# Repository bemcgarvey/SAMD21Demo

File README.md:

# SAMD21Demo
 
## A demonstartion board for the ATSAMD21G18A microcontroller.  Includes firmware projects to demonstrate many modules and features.  
  
### There is sample firmware for:
* Basic gpio and interrupts
* Sleepwalking
* Analog comparator
* PWM h-bridge control
* USB MSD device
* I2C LCD

### All firmware is built in MPLabX with MPLab Harmony 3 and the XC32 compiler.  
### Schematic and PCB were made with KiCAD

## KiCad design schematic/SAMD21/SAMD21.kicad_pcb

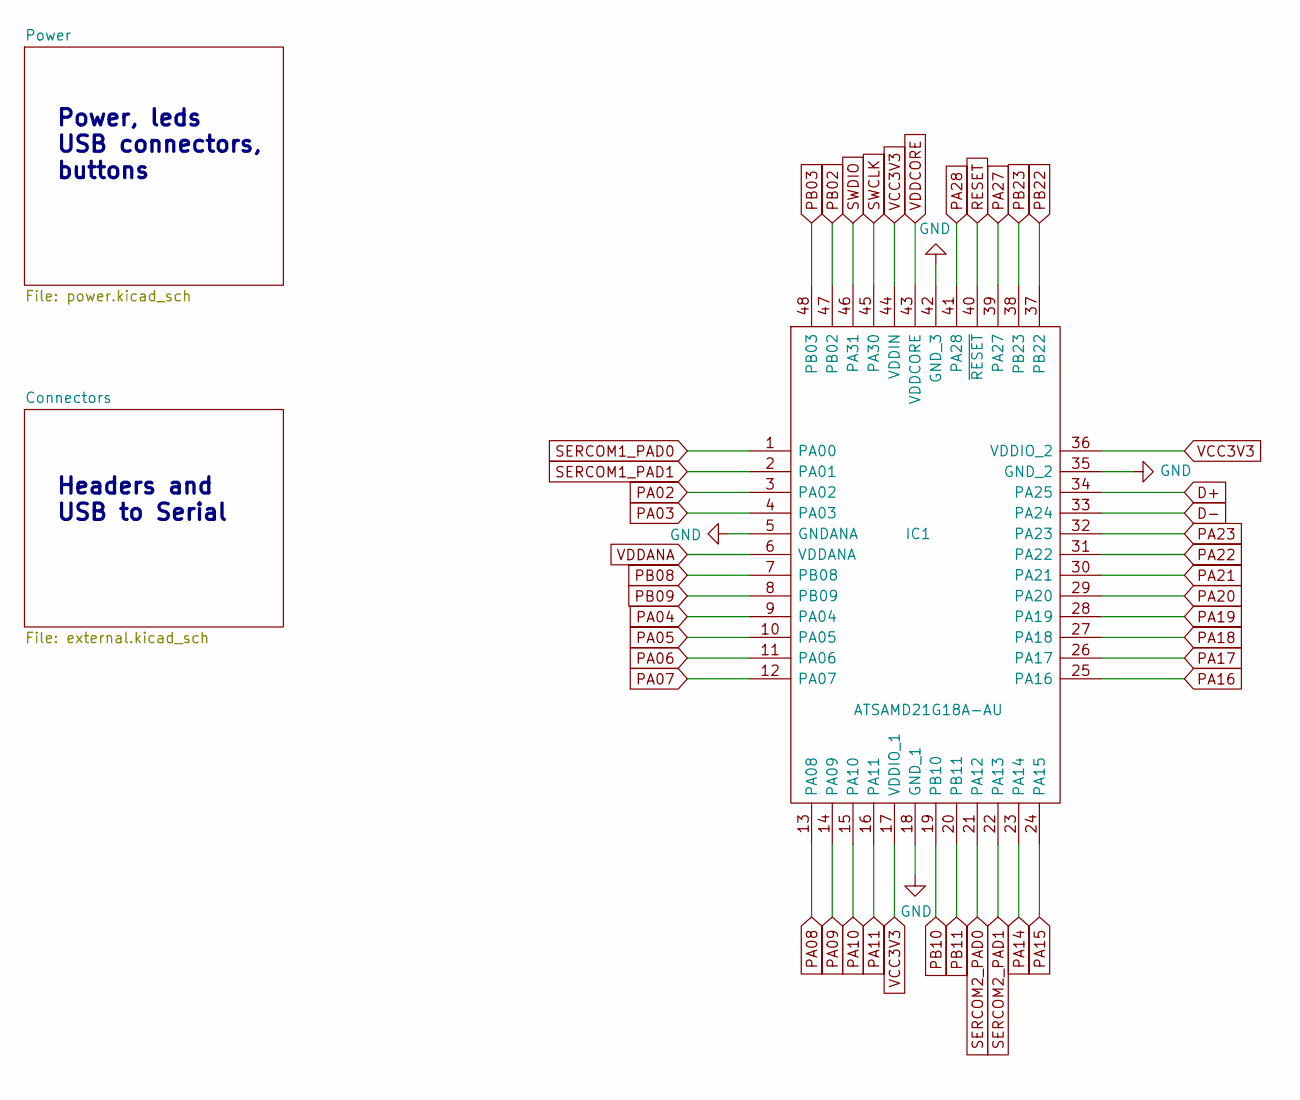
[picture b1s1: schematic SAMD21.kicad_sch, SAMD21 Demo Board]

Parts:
IC1: ATSAMD21G18A-AU; QFP50P900X900X120-48N; Mouser Part Number 556-ATSAMD21G18A-AU

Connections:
D+: IC1.34 (PA25); also elsewhere on the board
D-: IC1.33 (PA24); also elsewhere on the board
GND: IC1.5 (GNDANA), IC1.18 (GND_1), IC1.35 (GND_2), IC1.42 (GND_3); also elsewhere on the board
PA02: IC1.3 (PA02); also elsewhere on the board
PA03: IC1.4 (PA03); also elsewhere on the board
PA04: IC1.9 (PA04); also elsewhere on the board
PA05: IC1.10 (PA05); also elsewhere on the board
PA06: IC1.11 (PA06); also elsewhere on the board
PA07: IC1.12 (PA07); also elsewhere on the board
PA08: IC1.13 (PA08); also elsewhere on the board
PA09: IC1.14 (PA09); also elsewhere on the board
PA10: IC1.15 (PA10); also elsewhere on the board
PA11: IC1.16 (PA11); also elsewhere on the board
PA14: IC1.23 (PA14); also elsewhere on the board
PA15: IC1.24 (PA15); also elsewhere on the board
PA16: IC1.25 (PA16); also elsewhere on the board
PA17: IC1.26 (PA17); also elsewhere on the board
PA18: IC1.27 (PA18); also elsewhere on the board
PA19: IC1.28 (PA19); also elsewhere on the board
PA20: IC1.29 (PA20); also elsewhere on the board
PA21: IC1.30 (PA21); also elsewhere on the board
PA22: IC1.31 (PA22); also elsewhere on the board
PA23: IC1.32 (PA23); also elsewhere on the board
PA27: IC1.39 (PA27); also elsewhere on the board
PA28: IC1.41 (PA28); also elsewhere on the board
PB02: IC1.47 (PB02); also elsewhere on the board
PB03: IC1.48 (PB03); also elsewhere on the board
PB08: IC1.7 (PB08); also elsewhere on the board
PB09: IC1.8 (PB09); also elsewhere on the board
PB10: IC1.19 (PB10); also elsewhere on the board
PB11: IC1.20 (PB11); also elsewhere on the board
PB22: IC1.37 (PB22); also elsewhere on the board
PB23: IC1.38 (PB23); also elsewhere on the board
RESET: IC1.40 (~RESET); also elsewhere on the board
SERCOM1_PAD0: IC1.1 (PA00); also elsewhere on the board
SERCOM1_PAD1: IC1.2 (PA01); also elsewhere on the board
SERCOM2_PAD0: IC1.21 (PA12); also elsewhere on the board
SERCOM2_PAD1: IC1.22 (PA13); also elsewhere on the board
SWCLK: IC1.45 (PA30); also elsewhere on the board
SWDIO: IC1.46 (PA31); also elsewhere on the board
VCC3V3: IC1.17 (VDDIO_1), IC1.36 (VDDIO_2), IC1.44 (VDDIN); also elsewhere on the board
VDDANA: IC1.6 (VDDANA); also elsewhere on the board
VDDCORE: IC1.43 (VDDCORE); also elsewhere on the board

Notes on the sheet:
Headers and USB to Serial
Power, leds USB connectors, buttons

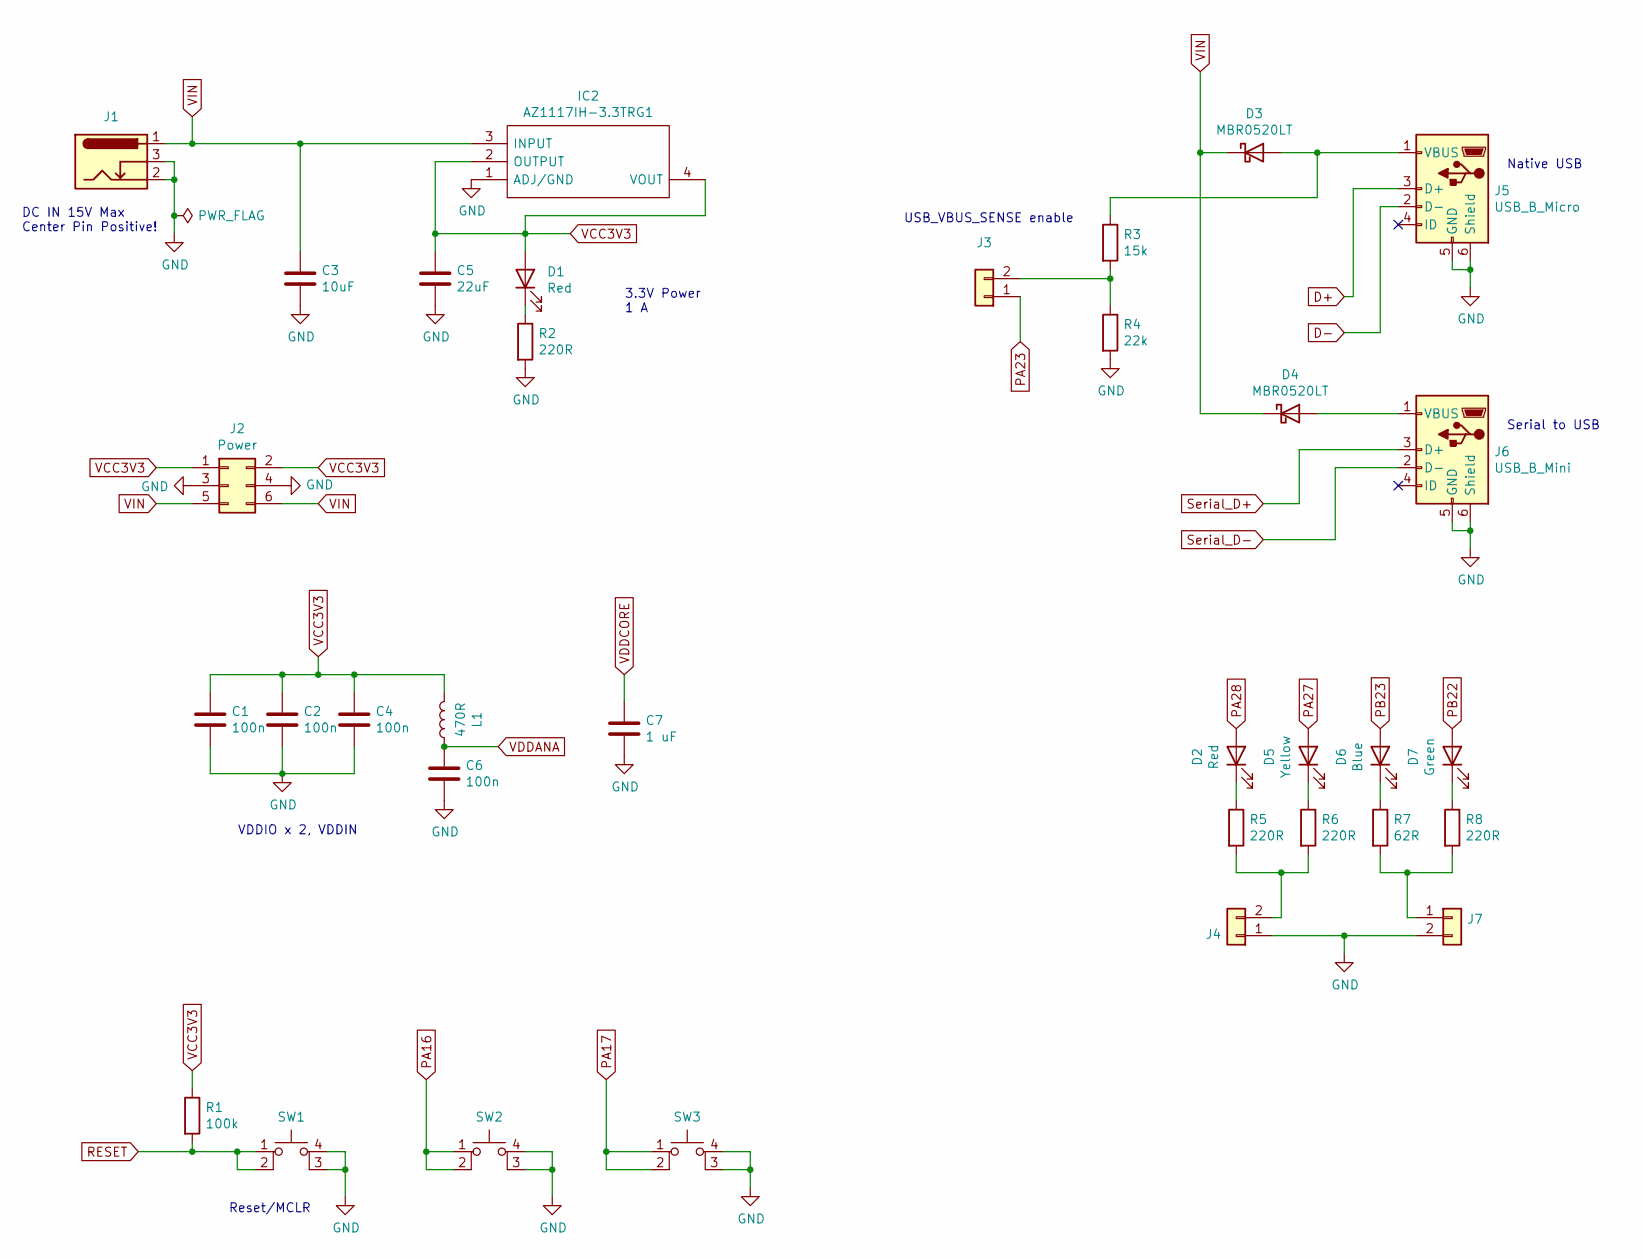
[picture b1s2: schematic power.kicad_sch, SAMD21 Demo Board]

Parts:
C1, C2, C4, C6: 100n; C_0402_1005Metric
C3: 10uF; C_0805_2012Metric
C5: 22uF; C_0603_1608Metric
C7: 1 uF; C_0402_1005Metric
D1: Red; LED_0603_1608Metric
D2: Red; LED_0805_2012Metric
D3, D4: MBR0520LT; D_SOD-123
D5: Yellow; LED_0805_2012Metric
D6: Blue; LED_0805_2012Metric
D7: Green; LED_0805_2012Metric
IC2: AZ1117IH-3.3TRG1; SOT230P700X180-4N; Mouser Part Number 621-AZ1117IH-3.3TRG1
J1: Barrel_Jack_Switch; BarrelJack_Wuerth_6941xx301002
J2: Power; PinHeader_2x03_P2.54mm_Vertical
J3, J4, J7: Conn_01x02; PinHeader_1x02_P2.54mm_Vertical
J5: USB_B_Micro; USB_Micro-B_Amphenol_10118194_Horizontal
J6: USB_B_Mini; USB_Mini-B_Wuerth_65100516121_Horizontal
L1: 470R; L_0603_1608Metric
R1: 100k; R_0603_1608Metric
R2, R5, R6, R8: 220R; R_0603_1608Metric
R3: 15k; R_0603_1608Metric
R4: 22k; R_0603_1608Metric
R7: 62R; R_0603_1608Metric
SW1: SW_MEC_5E; PTS647SK38SMTR2LFS
SW2, SW3: SW_MEC_5E; FSM16JH

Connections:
D+: J5.3 (D+); also elsewhere on the board
D-: J5.2 (D-); also elsewhere on the board
GND: C1.2, C2.2, C3.2, C4.2, C5.2, C6.2, C7.2, IC2.1 (ADJ/GND), J1.2, J1.3, J2.3, J2.4, J4.1, J5.5 (GND), J5.6 (Shield), J6.5 (GND), J6.6 (Shield), J7.2, R2.2, R4.2, SW1.3 (K), SW1.4 (A), SW2.3 (K), SW2.4 (A), SW3.3 (K), SW3.4 (A); also elsewhere on the board
unnamed: D1.1 (K), R2.1
unnamed: D2.1 (K), R5.1
unnamed: D3.2 (A), J5.1 (VBUS), R3.1
unnamed: D4.2 (A), J6.1 (VBUS)
unnamed: D5.1 (K), R6.1
unnamed: D6.1 (K), R7.1
unnamed: D7.1 (K), R8.1
unnamed: J3.2, R3.2, R4.1
unnamed: J4.2, R5.2, R6.2
unnamed: J7.1, R7.2, R8.2
PA16: SW2.1, SW2.2; also elsewhere on the board
PA17: SW3.1, SW3.2; also elsewhere on the board
PA23: J3.1; also elsewhere on the board
PA27: D5.2 (A); also elsewhere on the board
PA28: D2.2 (A); also elsewhere on the board
PB22: D7.2 (A); also elsewhere on the board
PB23: D6.2 (A); also elsewhere on the board
RESET: R1.2, SW1.1, SW1.2; also elsewhere on the board
Serial_D+: J6.3 (D+); also elsewhere on the board
Serial_D-: J6.2 (D-); also elsewhere on the board
VCC3V3: C1.1, C2.1, C4.1, C5.1, D1.2 (A), IC2.2 (OUTPUT), IC2.4 (VOUT), J2.1, J2.2, L1.2, R1.1; also elsewhere on the board
VDDANA: C6.1, L1.1; also elsewhere on the board
VDDCORE: C7.1; also elsewhere on the board
VIN: C3.1, D3.1 (K), D4.1 (K), IC2.3 (INPUT), J1.1, J2.5, J2.6

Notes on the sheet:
3.3V Power 1 A
Reset/MCLR
VDDIO x 2, VDDIN
Serial to USB
USB_VBUS_SENSE enable
DC IN 15V Max Center Pin Positive!
Native USB

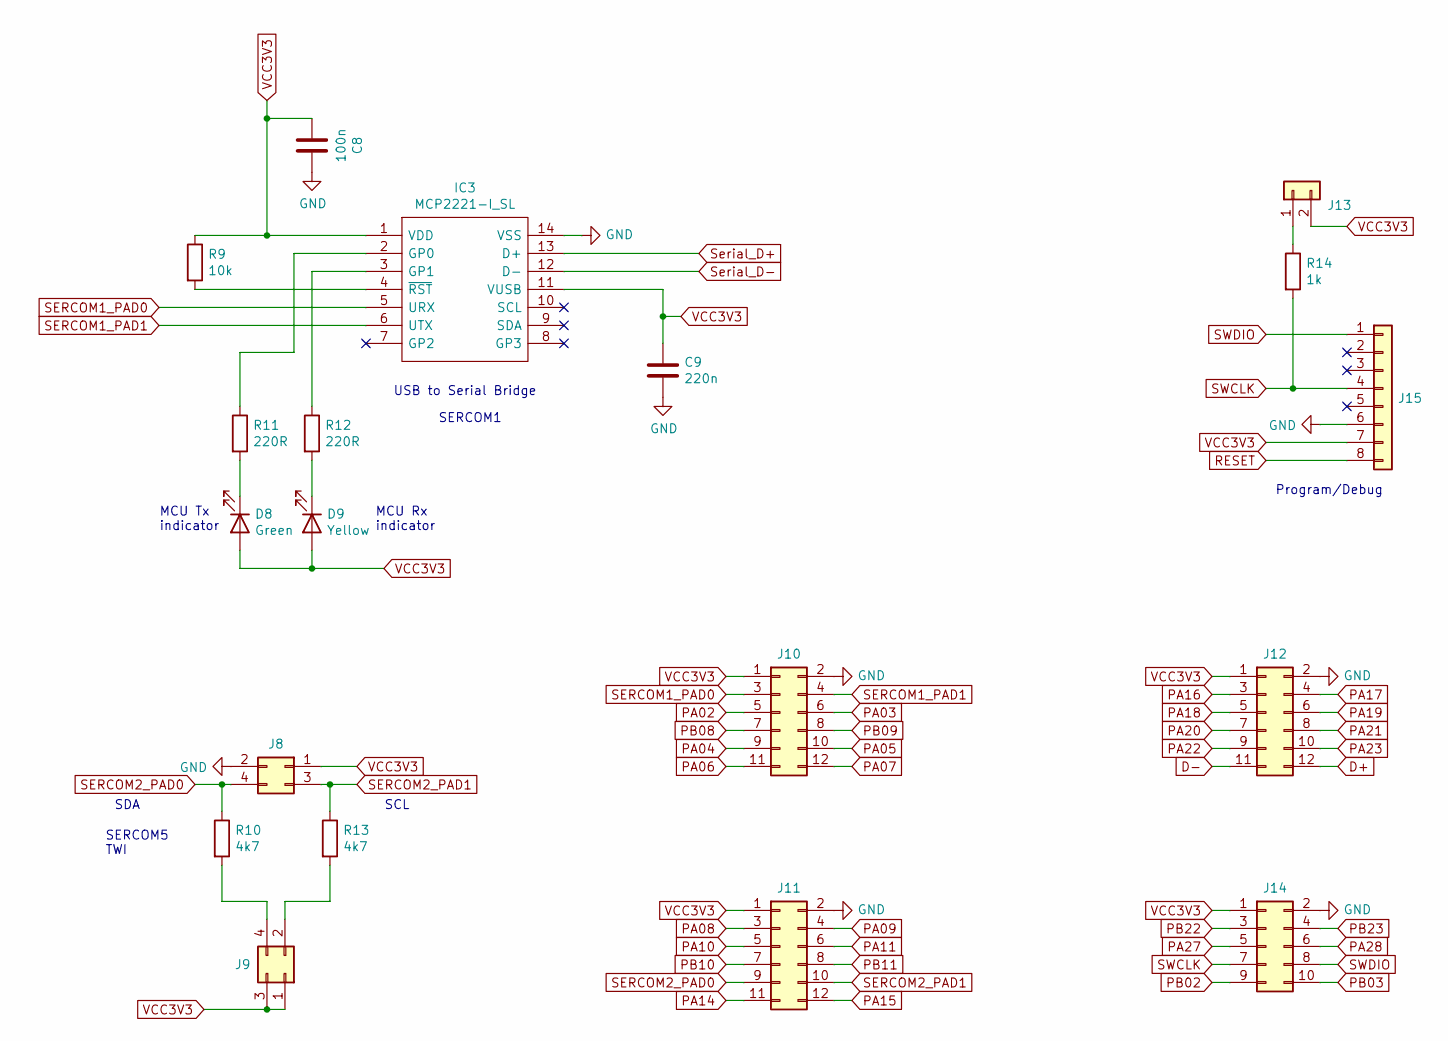
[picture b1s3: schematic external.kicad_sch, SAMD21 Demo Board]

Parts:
C8: 100n; C_0603_1608Metric
C9: 220n; C_0603_1608Metric
D8: Green; LED_0603_1608Metric
D9: Yellow; LED_0603_1608Metric
IC3: MCP2221-I_SL; SOIC127P600X175-14N; Mouser Part Number 579-MCP2221-I/SL
J8, J9: Conn_02x02_Odd_Even; PinHeader_2x02_P2.54mm_Vertical
J10, J11, J12: Conn_02x06_Odd_Even; PinHeader_2x06_P2.54mm_Vertical
J13: Conn_01x02; PinHeader_1x02_P2.54mm_Vertical
J14: Conn_02x05_Odd_Even; PinHeader_2x05_P2.54mm_Vertical
J15: Conn_01x08; PinHeader_1x08_P2.54mm_Horizontal
R9: 10k; R_0603_1608Metric
R10, R13: 4k7; R_0603_1608Metric
R11, R12: 220R; R_0603_1608Metric
R14: 1k; R_0603_1608Metric

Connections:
D+: J12.12; also elsewhere on the board
D-: J12.11; also elsewhere on the board
GND: C8.1, C9.2, IC3.14 (VSS), J8.2, J10.2, J11.2, J12.2, J14.2, J15.6; also elsewhere on the board
unnamed: D8.1 (K), R11.2
unnamed: D9.1 (K), R12.2
unnamed: IC3.2 (GP0), R11.1
unnamed: IC3.3 (GP1), R12.1
unnamed: IC3.4 (~RST), R9.2
unnamed: J9.2, R13.2
unnamed: J9.4, R10.2
unnamed: J13.1, R14.1
PA02: J10.5; also elsewhere on the board
PA03: J10.6; also elsewhere on the board
PA04: J10.9; also elsewhere on the board
PA05: J10.10; also elsewhere on the board
PA06: J10.11; also elsewhere on the board
PA07: J10.12; also elsewhere on the board
PA08: J11.3; also elsewhere on the board
PA09: J11.4; also elsewhere on the board
PA10: J11.5; also elsewhere on the board
PA11: J11.6; also elsewhere on the board
PA14: J11.11; also elsewhere on the board
PA15: J11.12; also elsewhere on the board
PA16: J12.3; also elsewhere on the board
PA17: J12.4; also elsewhere on the board
PA18: J12.5; also elsewhere on the board
PA19: J12.6; also elsewhere on the board
PA20: J12.7; also elsewhere on the board
PA21: J12.8; also elsewhere on the board
PA22: J12.9; also elsewhere on the board
PA23: J12.10; also elsewhere on the board
PA27: J14.5; also elsewhere on the board
PA28: J14.6; also elsewhere on the board
PB02: J14.9; also elsewhere on the board
PB03: J14.10; also elsewhere on the board
PB08: J10.7; also elsewhere on the board
PB09: J10.8; also elsewhere on the board
PB10: J11.7; also elsewhere on the board
PB11: J11.8; also elsewhere on the board
PB22: J14.3; also elsewhere on the board
PB23: J14.4; also elsewhere on the board
RESET: J15.8; also elsewhere on the board
SERCOM1_PAD0: IC3.5 (URX), J10.3; also elsewhere on the board
SERCOM1_PAD1: IC3.6 (UTX), J10.4; also elsewhere on the board
SERCOM2_PAD0: J8.4, J11.9, R10.1; also elsewhere on the board
SERCOM2_PAD1: J8.3, J11.10, R13.1; also elsewhere on the board
SWCLK: J14.7, J15.4, R14.2; also elsewhere on the board
SWDIO: J14.8, J15.1; also elsewhere on the board
Serial_D+: IC3.13 (D+); also elsewhere on the board
Serial_D-: IC3.12 (D-); also elsewhere on the board
VCC3V3: C8.2, C9.1, D8.2 (A), D9.2 (A), IC3.1 (VDD), IC3.11 (VUSB), J8.1, J9.1, J9.3, J10.1, J11.1, J12.1, J13.2, J14.1, J15.7, R9.1; also elsewhere on the board

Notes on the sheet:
MCU Tx indicator
SCL
USB to Serial Bridge
SDA
MCU Rx indicator
SERCOM5 TWI
Program/Debug
SERCOM1

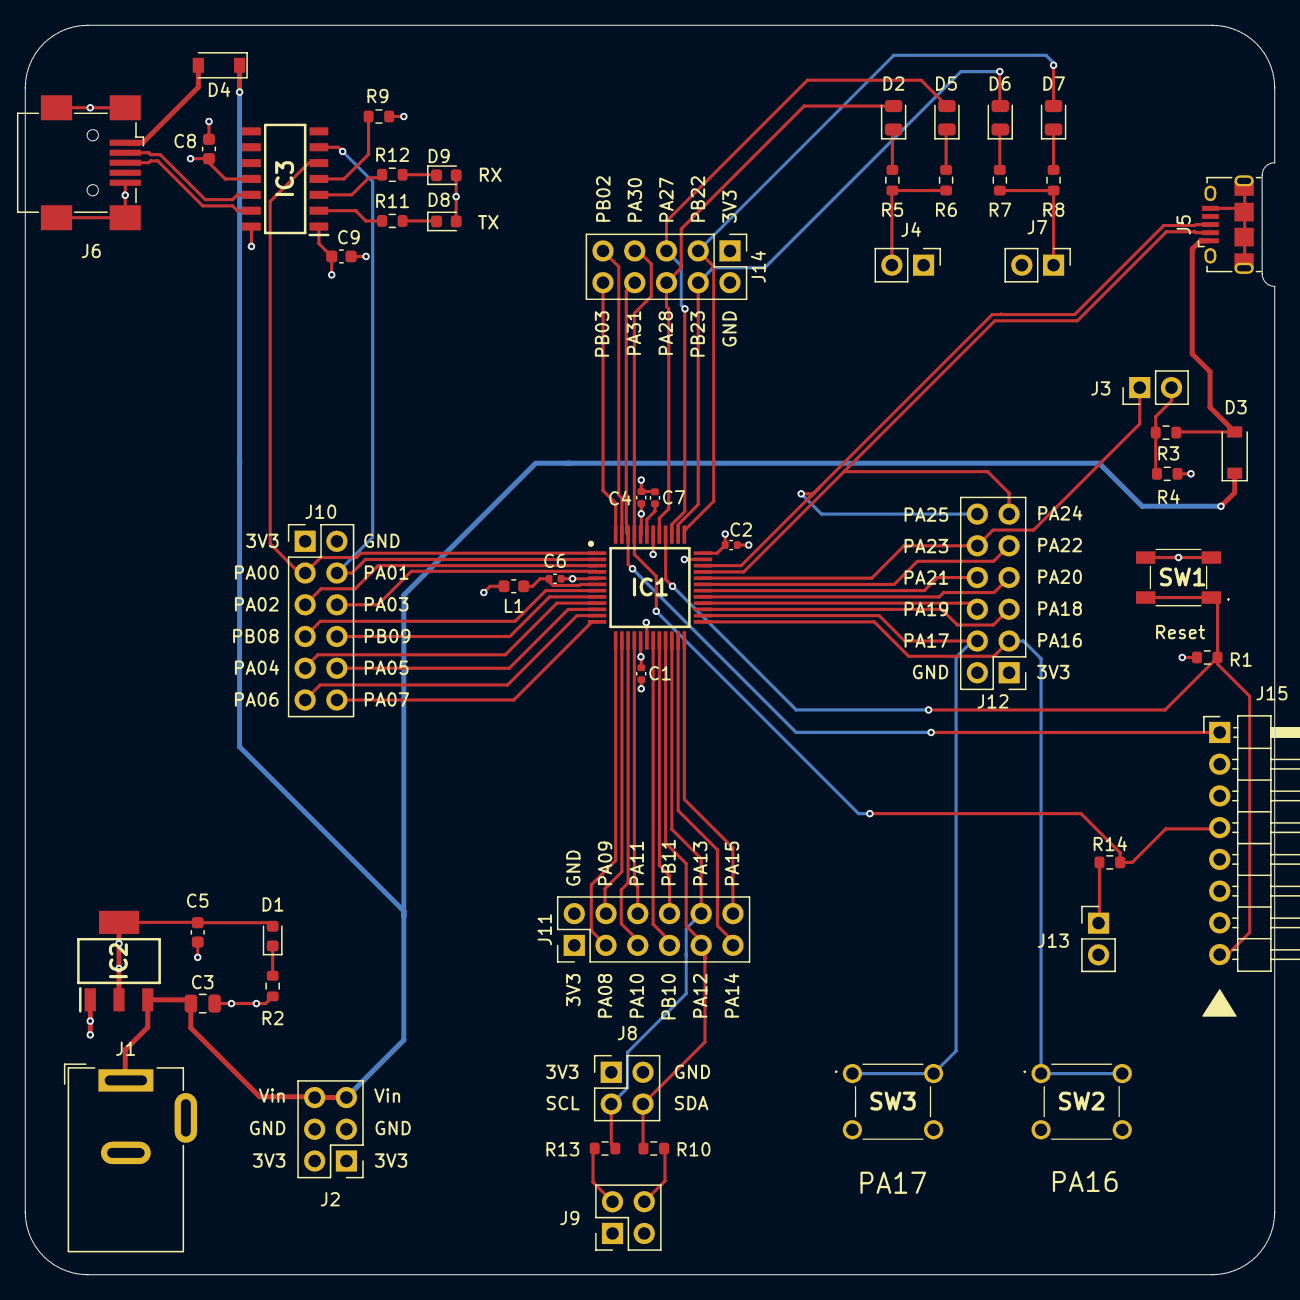
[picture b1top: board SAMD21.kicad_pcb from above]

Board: 4 copper layers, 100.0 x 100.0 mm, 54 parts (0 on the bottom side), 64 nets.

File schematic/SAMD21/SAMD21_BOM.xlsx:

Ref | Qnty | Value | Footprint
C1, C2, C4, C6, | 4 | 100n | Capacitor_SMD:C_0402_1005Metric
C3, | 1 | 10uF | Capacitor_SMD:C_0805_2012Metric
C5, | 1 | 22uF | Capacitor_SMD:C_0603_1608Metric
C7, | 1 | 1 uF | Capacitor_SMD:C_0402_1005Metric
C8, | 1 | 100n | Capacitor_SMD:C_0603_1608Metric
C9, | 1 | 220n | Capacitor_SMD:C_0603_1608Metric
D1, | 1 | Red | LED_SMD:LED_0603_1608Metric
D2, | 1 | Red | LED_SMD:LED_0805_2012Metric
D3, D4, | 2 | MBR0520LT | Diode_SMD:D_SOD-123
D5, | 1 | Yellow | LED_SMD:LED_0805_2012Metric
D6, | 1 | Blue | LED_SMD:LED_0805_2012Metric
D7, | 1 | Green | LED_SMD:LED_0805_2012Metric
D8, | 1 | Green | LED_SMD:LED_0603_1608Metric
D9, | 1 | Yellow | LED_SMD:LED_0603_1608Metric
IC1, | 1 | ATSAMD21G18A-AU | SamacSys_Parts:QFP50P900X900X120-48N
IC2, | 1 | AZ1117IH-3.3TRG1 | SamacSys_Parts:SOT230P700X180-4N
IC3, | 1 | MCP2221-I_SL | SamacSys_Parts:SOIC127P600X175-14N
J1, | 1 | Barrel_Jack_Switch | Connector_BarrelJack:BarrelJack_Wuerth_6941xx301002
J2, | 1 | Power | Connector_PinHeader_2.54mm:PinHeader_2x03_P2.54mm_Vertical
J3, J4, J7, J13, | 4 | Conn_01x02 | Connector_PinHeader_2.54mm:PinHeader_1x02_P2.54mm_Vertical
J5, | 1 | USB_B_Micro | Connector_USB:USB_Micro-B_Amphenol_10118194_Horizontal
J6, | 1 | USB_B_Mini | Connector_USB:USB_Mini-B_Wuerth_65100516121_Horizontal
J8, J9, | 2 | Conn_02x02_Odd_Even | Connector_PinHeader_2.54mm:PinHeader_2x02_P2.54mm_Vertical
J10, J11, J12, | 3 | Conn_02x06_Odd_Even | Connector_PinHeader_2.54mm:PinHeader_2x06_P2.54mm_Vertical
J14, | 1 | Conn_02x05_Odd_Even | Connector_PinHeader_2.54mm:PinHeader_2x05_P2.54mm_Vertical
J15, | 1 | Conn_01x08 | Connector_PinHeader_2.54mm:PinHeader_1x08_P2.54mm_Horizontal
L1, | 1 | 470R | Inductor_SMD:L_0603_1608Metric
R1, | 1 | 100k | Resistor_SMD:R_0603_1608Metric
R2, R5, R6, R8, R11, R12, | 6 | 220R | Resistor_SMD:R_0603_1608Metric
R3, | 1 | 15k | Resistor_SMD:R_0603_1608Metric
R4, | 1 | 22k | Resistor_SMD:R_0603_1608Metric
R7, | 1 | 62R | Resistor_SMD:R_0603_1608Metric
R9, | 1 | 10k | Resistor_SMD:R_0603_1608Metric
R10, R13, | 2 | 4k7 | Resistor_SMD:R_0603_1608Metric
R14, | 1 | 1k | Resistor_SMD:R_0603_1608Metric
SW1, | 1 | SW_MEC_5E | SamacSys_Parts:PTS647SK38SMTR2LFS
SW2, SW3, | 2 | SW_MEC_5E | SamacSys_Parts:FSM16JH

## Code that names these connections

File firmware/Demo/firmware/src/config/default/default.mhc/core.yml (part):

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    - type: Values
      children:
      - type: Dynamic
        attributes: {id: core, value: PA00}
  - type: String
    attributes: {id: PORT_GROUP_0_PAD_1}
    children:
    - type: Values
      children:
      - type: Dynamic
        attributes: {id: core, value: PA01}
  - type: String
    attributes: {id: PORT_GROUP_0_PAD_10}
    children:
    - type: Values
      children:
      - type: Dynamic
        attributes: {id: core, value: PA10}
  - type: String
    attributes: {id: PORT_GROUP_0_PAD_11}
    children:
    - type: Values
      children:
      - type: Dynamic
        attributes: {id: core, value: PA11}
  - type: String
    attributes: {id: PORT_GROUP_0_PAD_12}
    children:
    - type: Values
      children:
      - type: Dynamic
        attributes: {id: core, value: PA12}
  - type: String
    attributes: {id: PORT_GROUP_0_PAD_13}
    children:
    - type: Values
      children:
      - type: Dynamic
        attributes: {id: core, value: PA13}
  - type: String
    attributes: {id: PORT_GROUP_0_PAD_16}
    children:
    - type: Values
      children:
      - type: Dynamic
        attributes: {id: core, value: PA16}
  - type: String
    attributes: {id: PORT_GROUP_0_PAD_17}
    children:
    - type: Values
      children:
      - type: Dynamic
        attributes: {id: core, value: PA17}
  - type: String
    attributes: {id: PORT_GROUP_0_PAD_20}
    children:
    - type: Values
      children:
      - type: Dynamic
        attributes: {id: core, value: PA20}
  - type: String
    attributes: {id: PORT_GROUP_0_PAD_21}
    children:
    - type: Values
      children:
      - type: Dynamic
        attributes: {id: core, value: PA21}
  - type: String
    attributes: {id: PORT_GROUP_0_PAD_27}
    children:
    - type: Values
      children:
      - type: Dynamic
        attributes: {id: core, value: PA27}
  - type: String
    attributes: {id: PORT_GROUP_0_PAD_28}
    children:
    - type: Values
      children:
      - type: Dynamic
        attributes: {id: core, value: PA28}
  - type: String
    attributes: {id: PORT_GROUP_0_PAD_4}
    children:
    - type: Values
      children:
      - type: Dynamic
        attributes: {id: core, value: PA04}
  - type: String
    attributes: {id: PORT_GROUP_0_PAD_6}
    children:
    - type: Values
      children:
      - type: Dynamic
        attributes: {id: core, value: PA06}
  - type: String
    attributes: {id: PORT_GROUP_0_PAD_7}
    children:
    - type: Values
      children:
      - type: Dynamic
        attributes: {id: core, value: PA07}
  - type: String
    attributes: {id: PORT_GROUP_0_PAD_8}
    children:
    - type: Values
      children:
      - type: Dynamic
        attributes: {id: core, value: PA08}
  - type: String
    attributes: {id: PORT_GROUP_0_PAD_9}
    children:
    - type: Values
      children:
      - type: Dynamic
        attributes: {id: core, value: PA09}
  - type: String
    attributes: {id: PORT_GROUP_0_PINCFG0}
    children:
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    - type: Values
      children:
      - type: Dynamic
        attributes: {id: core, value: PB10}
  - type: String
    attributes: {id: PORT_GROUP_1_PAD_11}
    children:
    - type: Values
      children:
      - type: Dynamic
        attributes: {id: core, value: PB11}
  - type: String
    attributes: {id: PORT_GROUP_1_PAD_22}
    children:
    - type: Values
      children:
      - type: Dynamic
        attributes: {id: core, value: PB22}
  - type: String
    attributes: {id: PORT_GROUP_1_PAD_23}
    children:
    - type: Values
      children:
      - type: Dynamic
        attributes: {id: core, value: PB23}
  - type: String
    attributes: {id: PORT_GROUP_1_PINCFG10}
    children:
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
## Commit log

2021-11-14 Initial project
2021-11-16 Partial schematic
2021-11-17 Complete schematic
2021-11-17 Moved I2C to pins with support for I2C
2021-11-20 Initial pcb layout
2021-11-25 Minor trace adjustments and some labels
2021-11-27 Finished silkscreen
2021-11-28 Changed LEDs to 0805
2022-01-02 minor fix
2022-01-02 Changed USB micro footprint
2022-01-02 Generated gerbers
2022-01-19 Converted to KiCad 6
2022-01-20 Added errata
2022-01-20 Added BOM
2022-01-21 Initial demo code
2022-01-21 Added lcd
2022-01-22 Added MSD demo
2022-01-22 Added sleepwalking demo
2022-01-22 Added AC demo
2022-01-23 Added TCC h-bridge pwm
2022-01-24 Added SPI eeprom demo
2022-01-27 Some cleanup
2022-01-27 Added MSD with SPI eeprom demo
